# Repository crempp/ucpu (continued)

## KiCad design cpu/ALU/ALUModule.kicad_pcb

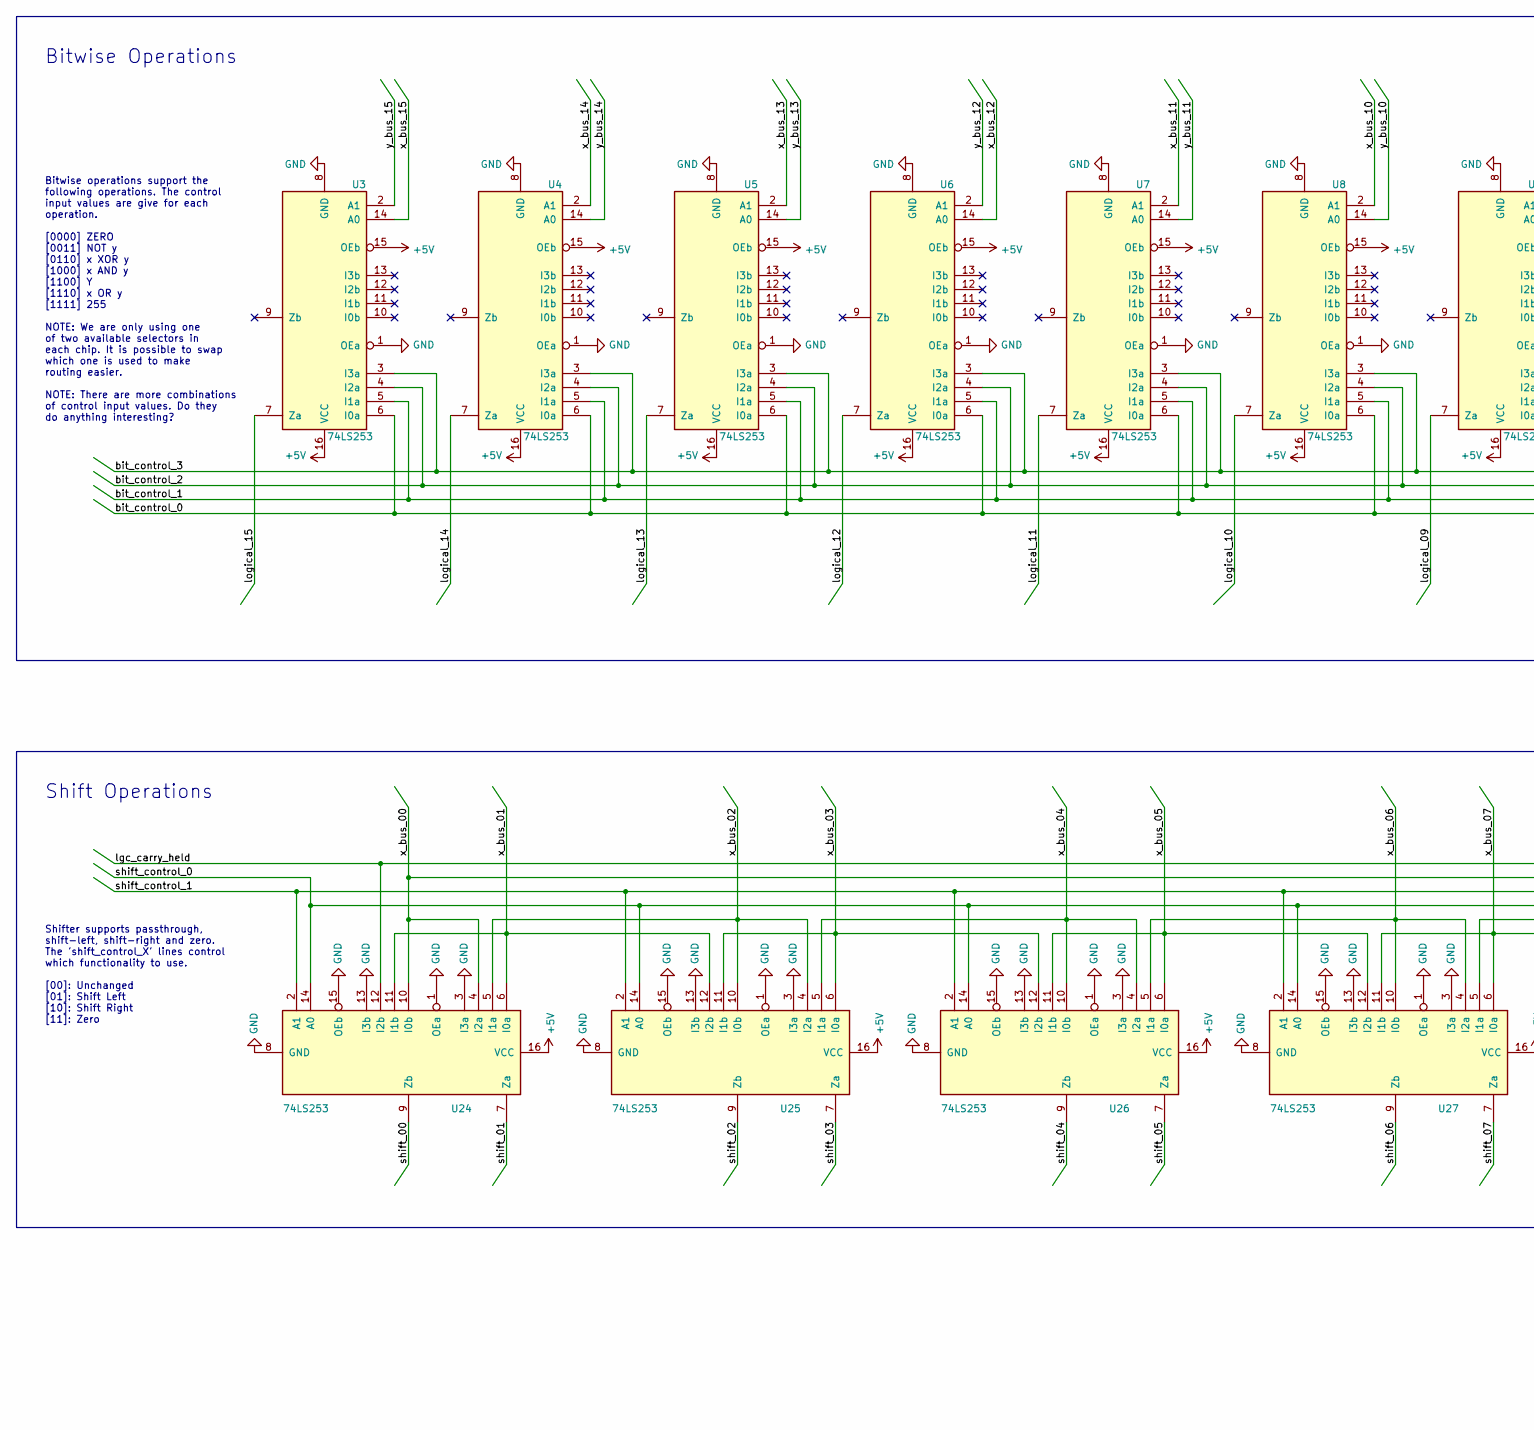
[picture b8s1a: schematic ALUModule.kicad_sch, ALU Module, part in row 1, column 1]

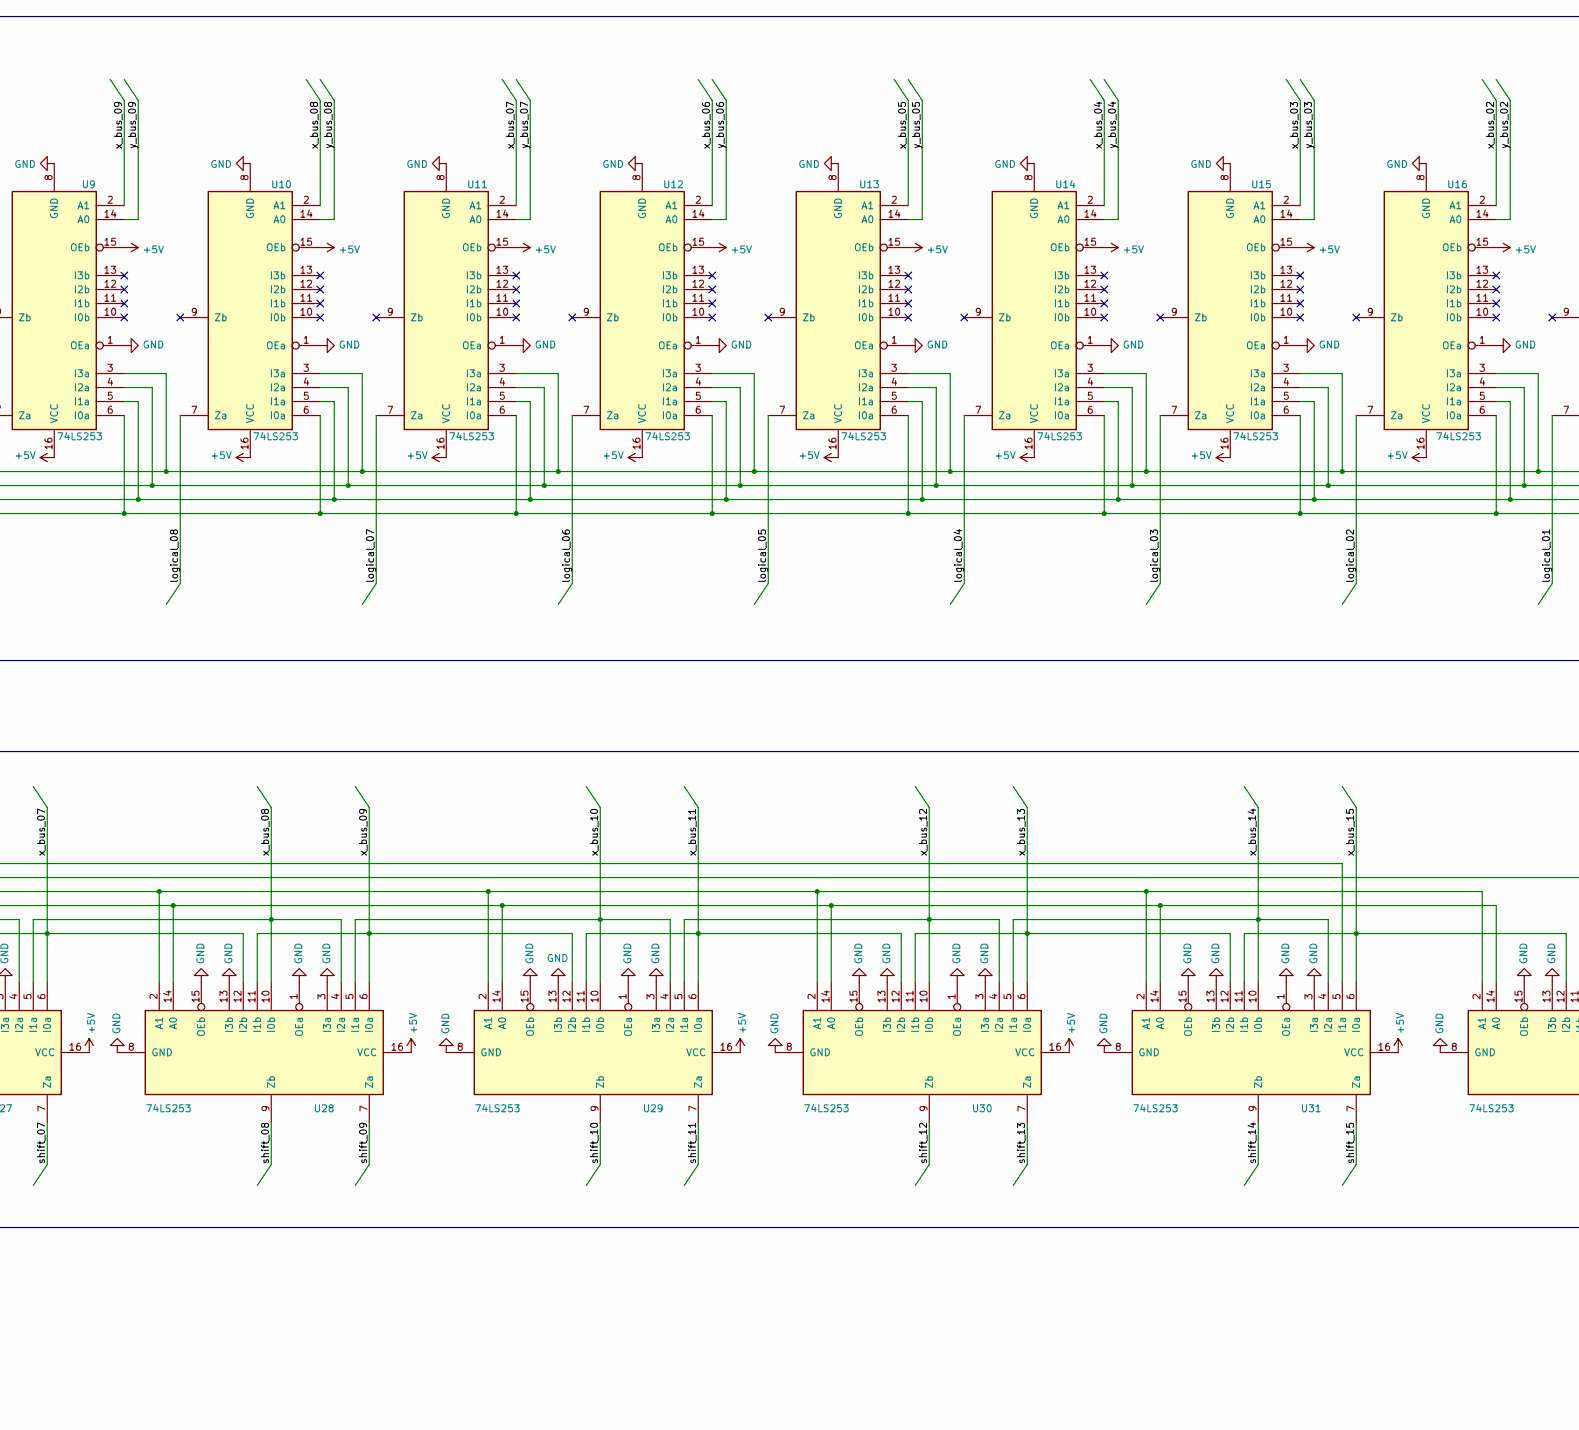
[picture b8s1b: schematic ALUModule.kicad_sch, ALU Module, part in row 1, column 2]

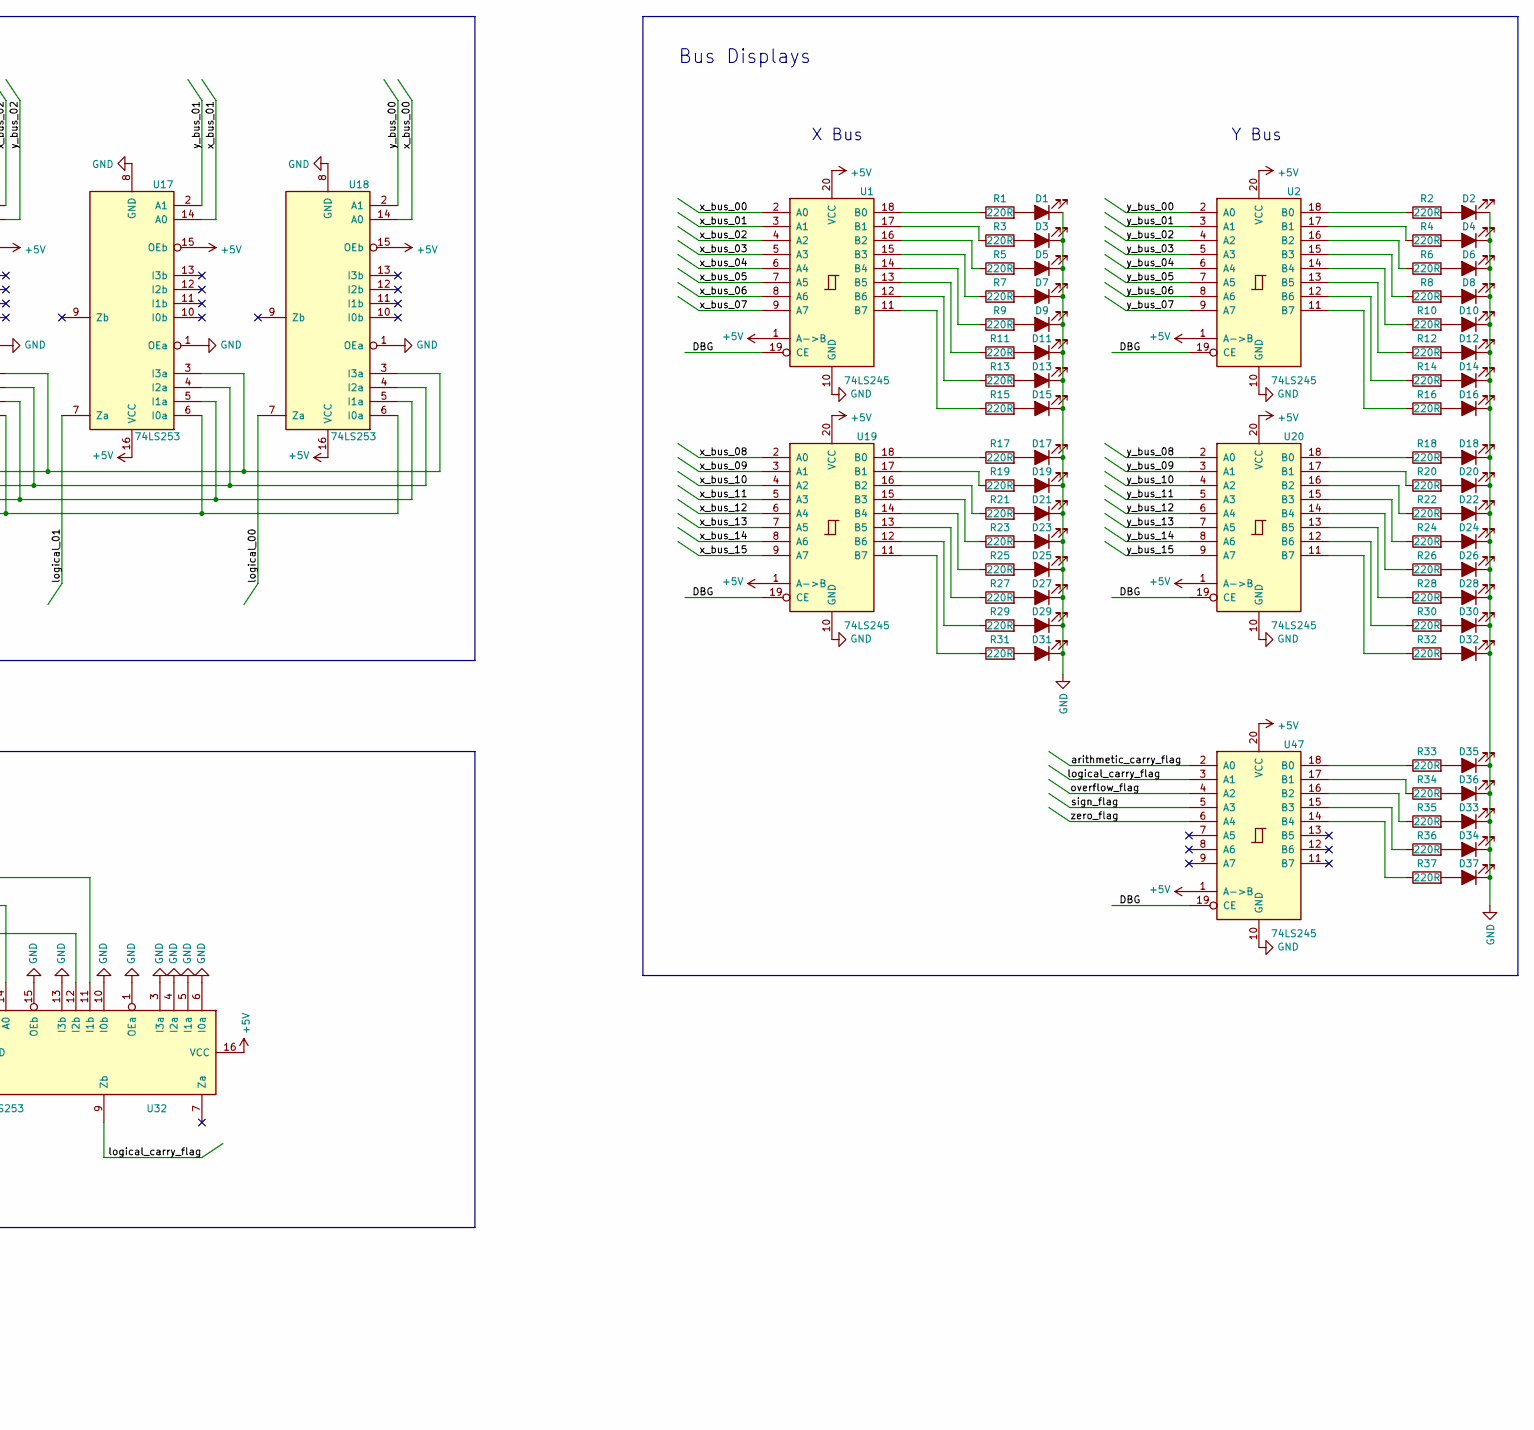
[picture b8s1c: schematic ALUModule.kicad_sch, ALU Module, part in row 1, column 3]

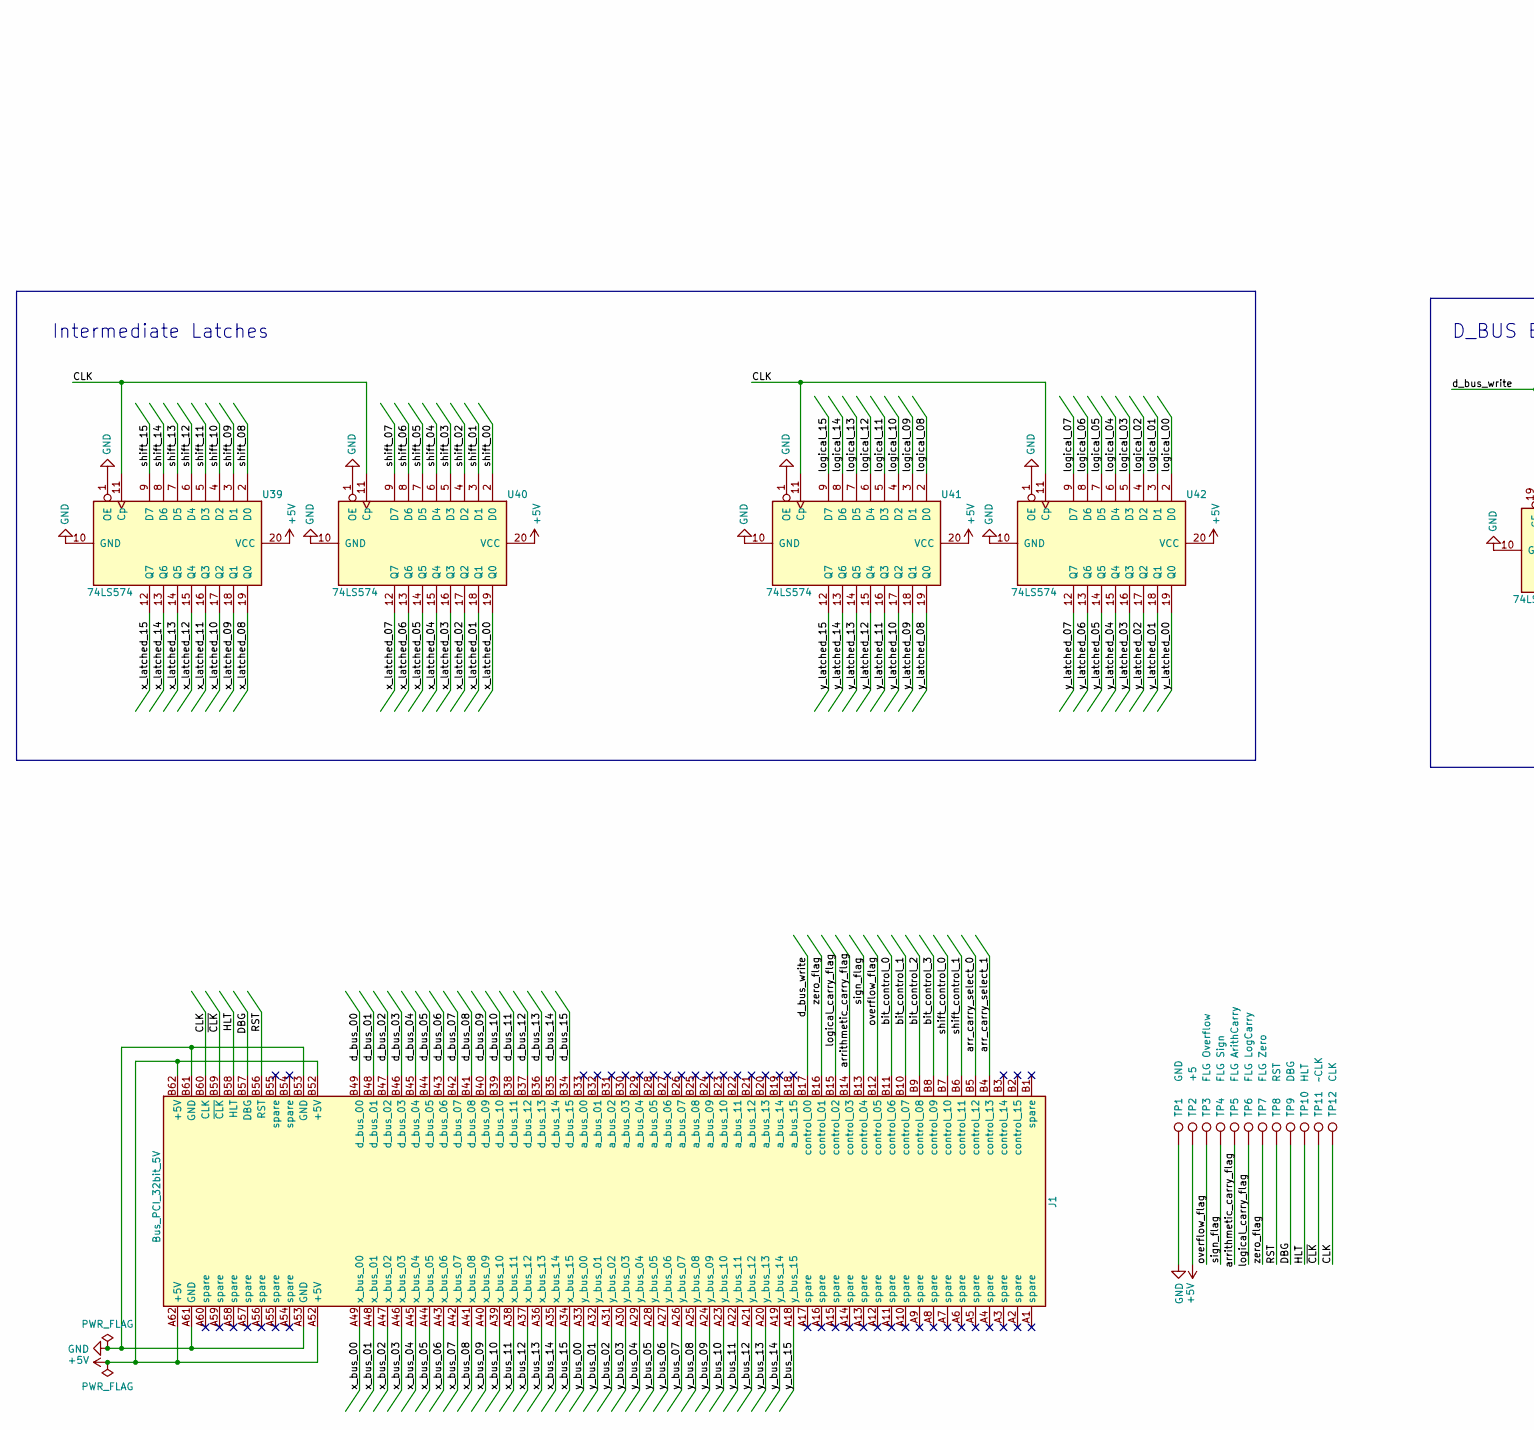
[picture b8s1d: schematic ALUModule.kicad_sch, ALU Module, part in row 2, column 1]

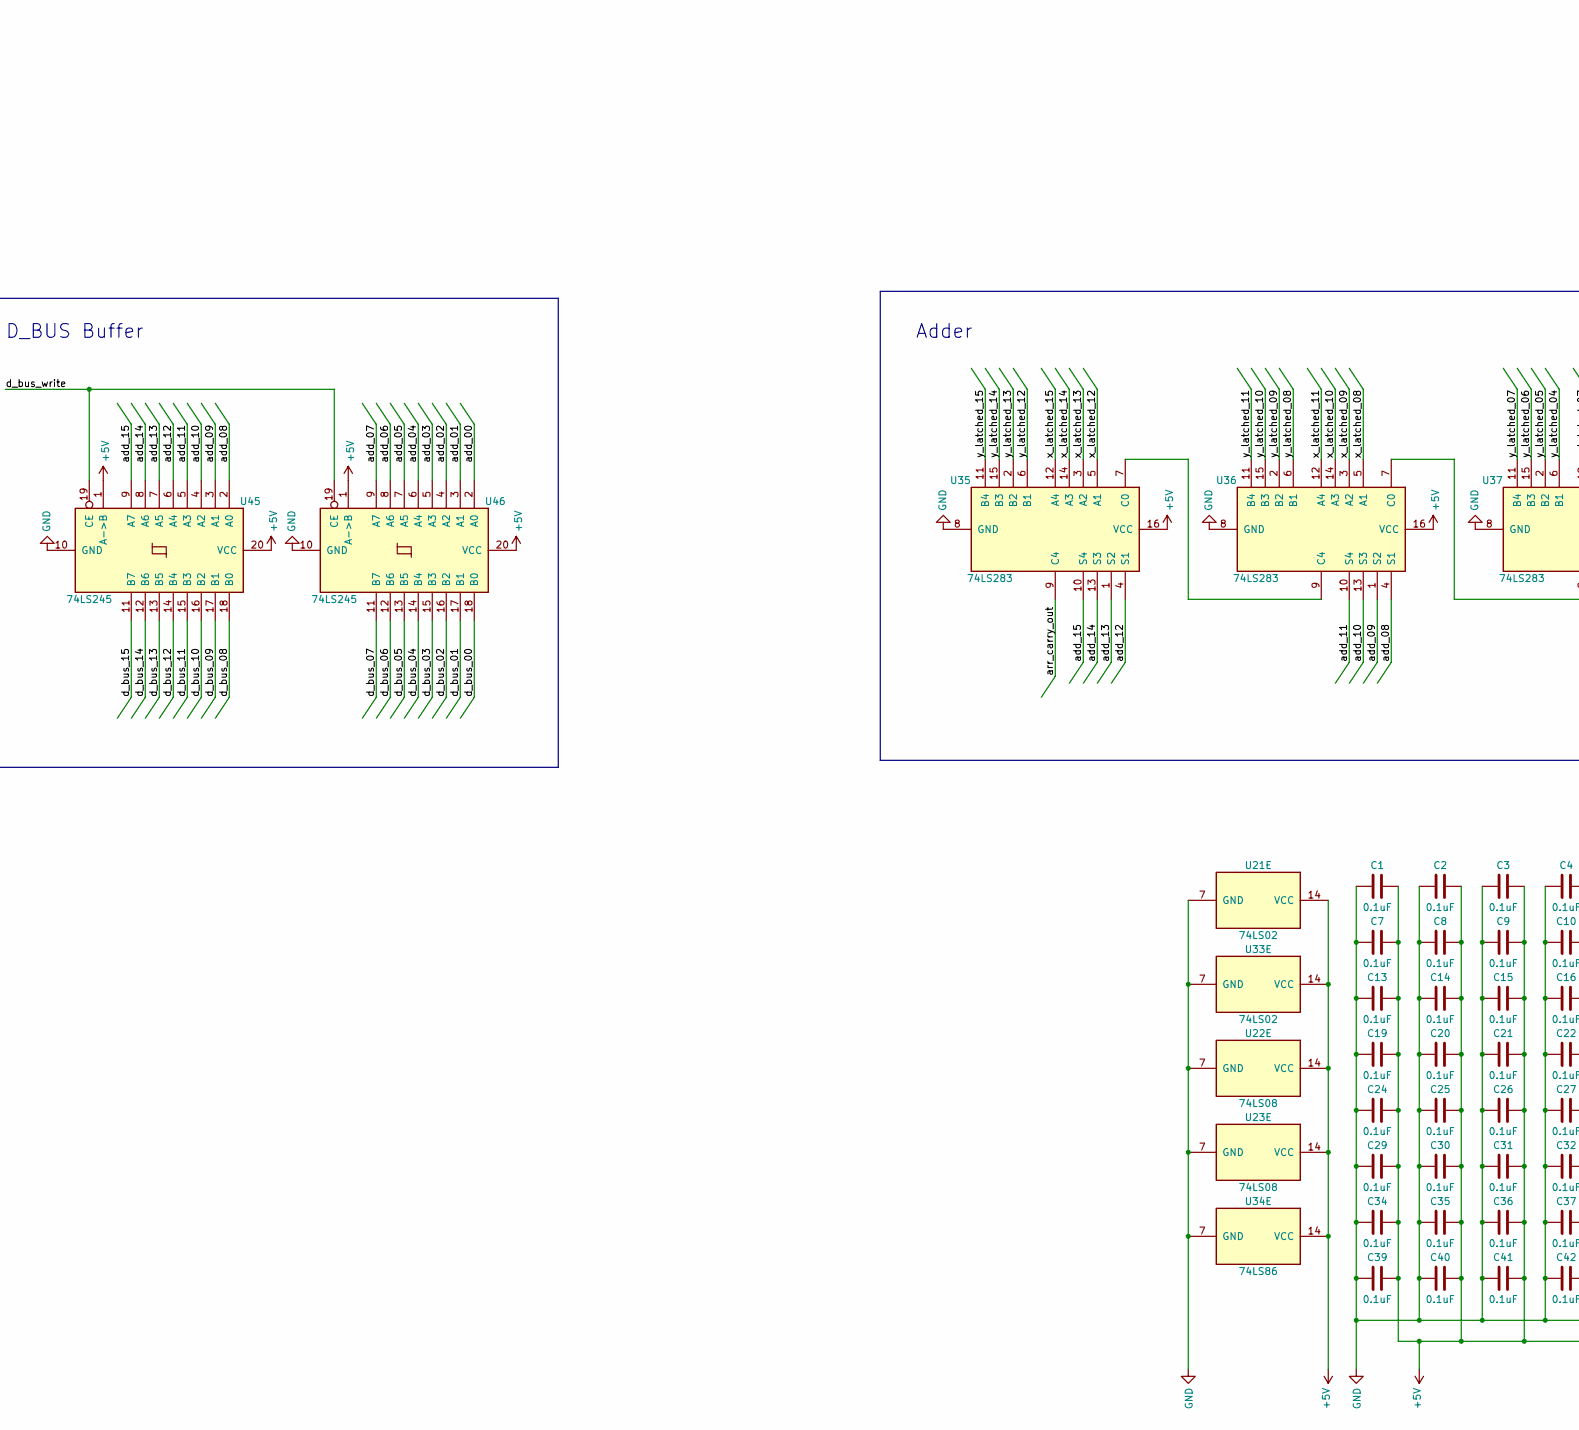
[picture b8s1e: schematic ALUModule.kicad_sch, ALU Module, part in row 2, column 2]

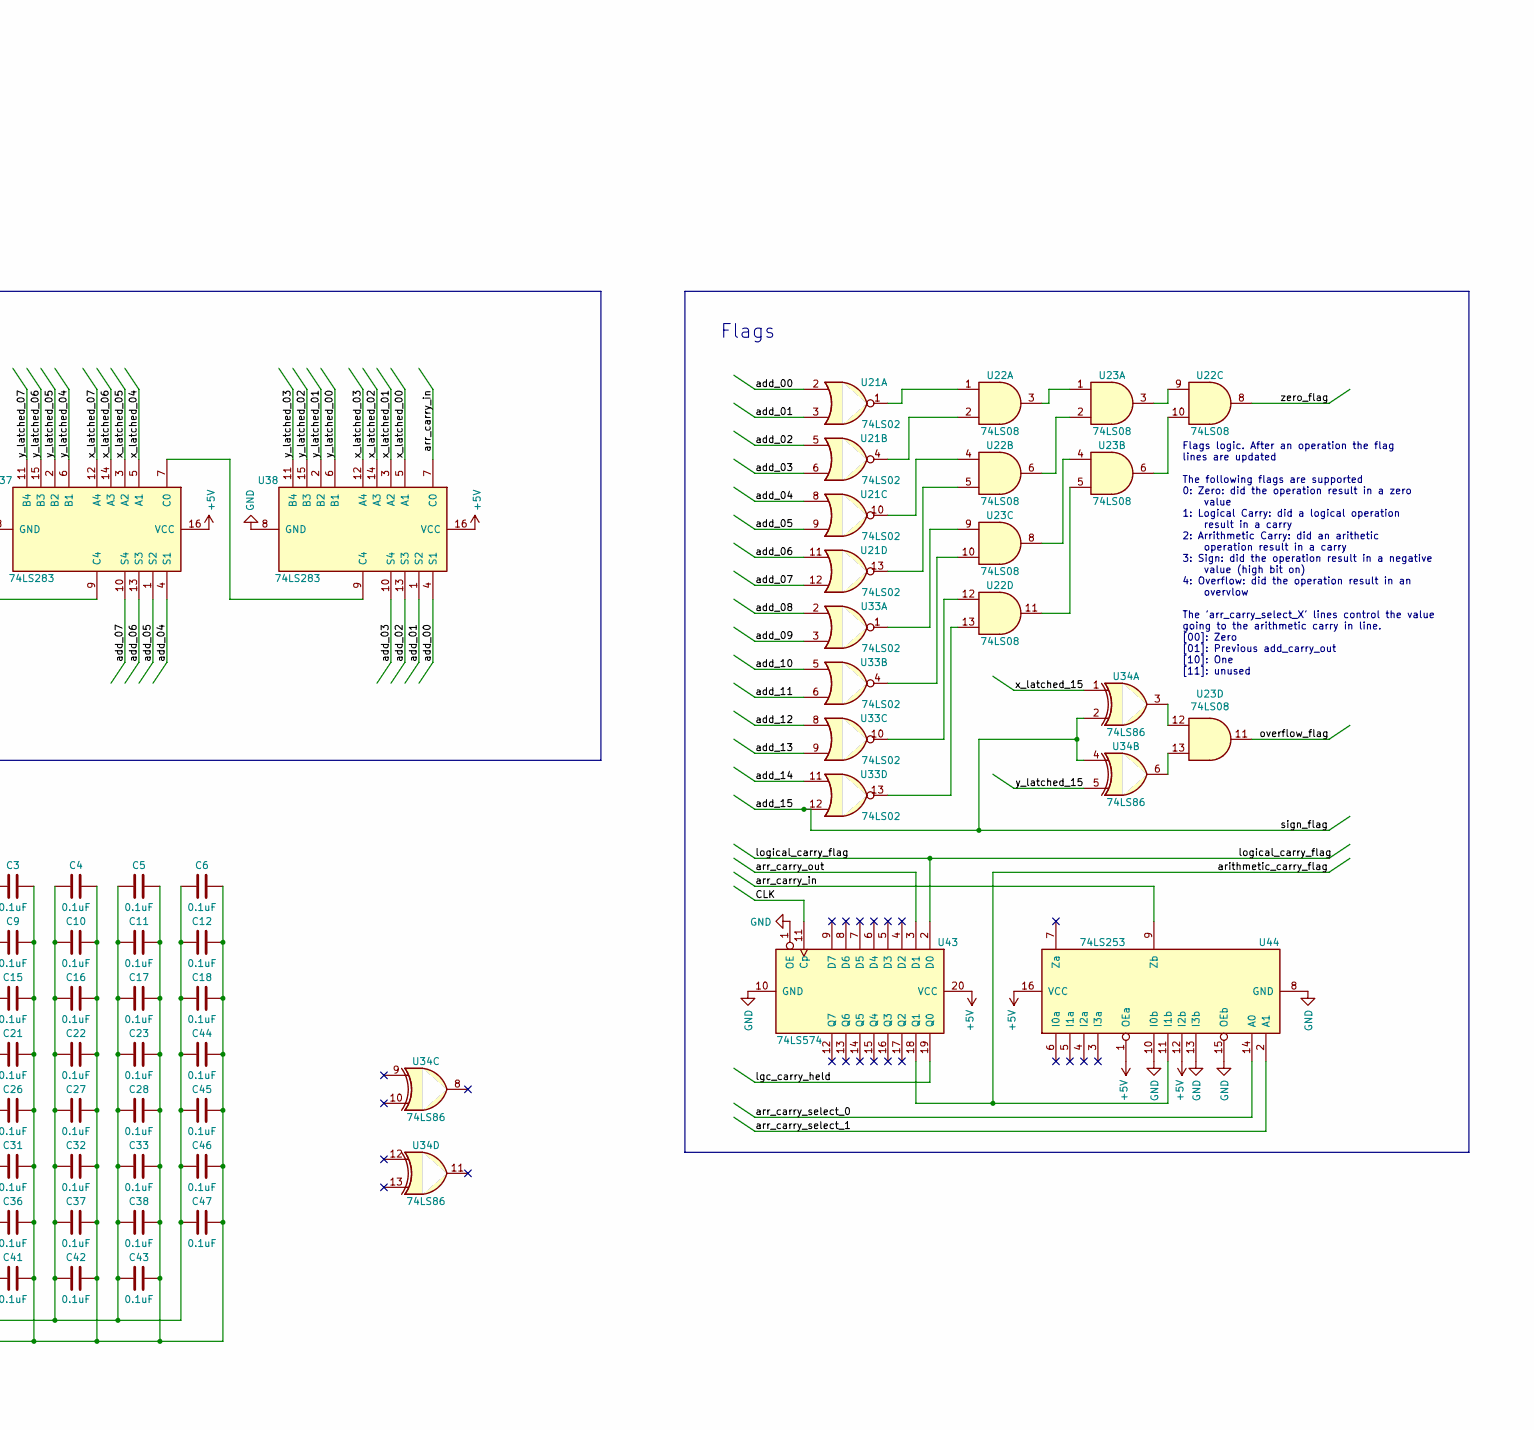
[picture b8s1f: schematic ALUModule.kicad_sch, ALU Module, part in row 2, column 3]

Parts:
C1, C2, C3, C4, C5, C6, C7, C8, C9, C10, C11, C12, C13, C14, C15, C16, C17, C18, C19, C20, C21, C22, C23, C24, C25, C26, C27, C28, C29, C30, C31, C32, C33, C34, C35, C36, C37, C38, C39, C40, C41, C42, C43, C44, C45, C46, C47: 0.1uF; C_0603_1608Metric_Pad1.05x0.95mm_HandSolder
D1, D2, D3, D4, D5, D6, D7, D8, D9, D10, D11, D12, D13, D14, D15, D16, D17, D18, D19, D20, D21, D22, D23, D24, D25, D26, D27, D28, D29, D30, D31, D32: LED_ALT; LED_1206_3216Metric_Pad1.42x1.75mm_HandSolder
D33: overflow; LED_1206_3216Metric_Pad1.42x1.75mm_HandSolder
D34: sign; LED_1206_3216Metric_Pad1.42x1.75mm_HandSolder
D35: arithmetic_carry; LED_1206_3216Metric_Pad1.42x1.75mm_HandSolder
D36: logical_carry; LED_1206_3216Metric_Pad1.42x1.75mm_HandSolder
D37: zero; LED_1206_3216Metric_Pad1.42x1.75mm_HandSolder
J1: Bus_PCI_32bit_5V; BUS_PCI
R1, R2, R3, R4, R5, R6, R7, R8, R9, R10, R11, R12, R13, R14, R15, R16, R17, R18, R19, R20, R21, R22, R23, R24, R25, R26, R27, R28, R29, R30, R31, R32, R33, R34, R35, R36, R37: 220R; R_0603_1608Metric_Pad1.05x0.95mm_HandSolder
TP1: GND; TestPoint_Pad_D1.5mm
TP2: +5; TestPoint_Pad_D1.5mm
TP3: FLG Overflow; TestPoint_Pad_D1.5mm
TP4: FLG Sign; TestPoint_Pad_D1.5mm
TP5: FLG ArithCarry; TestPoint_Pad_D1.5mm
TP6: FLG LogCarry; TestPoint_Pad_D1.5mm
TP7: FLG Zero; TestPoint_Pad_D1.5mm
TP8: RST; TestPoint_Pad_D1.5mm
TP9: DBG; TestPoint_Pad_D1.5mm
TP10: HLT; TestPoint_Pad_D1.5mm
TP11: ~CLK; TestPoint_Pad_D1.5mm
TP12: CLK; TestPoint_Pad_D1.5mm
U1, U2, U19, U20, U45, U46, U47: 74LS245; SOIC-20W_7.5x12.8mm_P1.27mm
U3, U4, U5, U6, U7, U8, U9, U10, U11, U12, U13, U14, U15, U16, U17, U18, U24, U25, U26, U27, U28, U29, U30, U31, U32, U44: 74LS253; SOIC-16_3.9x9.9mm_P1.27mm
U21, U33: 74LS02; SOIC-14_3.9x8.7mm_P1.27mm
U22, U23: 74LS08; SOIC-14_3.9x8.7mm_P1.27mm
U34: 74LS86; SOIC-14_3.9x8.7mm_P1.27mm
U35, U36, U37, U38: 74LS283; SOIC-16_3.9x9.9mm_P1.27mm
U39, U40, U41, U42, U43: 74LS574; SOIC-20W_7.5x12.8mm_P1.27mm

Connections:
+5V: C1.1, C2.1, C3.1, C4.1, C5.1, C6.1, C7.1, C8.1, C9.1, C10.1, C11.1, C12.1, C13.1, C14.1, C15.1, C16.1, C17.1, C18.1, C19.1, C20.1, C21.1, C22.1, C23.1, C24.1, C25.1, C26.1, C27.1, C28.1, C29.1, C30.1, C31.1, C32.1, C33.1, C34.1, C35.1, C36.1, C37.1, C38.1, C39.1, C40.1, C41.1, C42.1, C43.1, C44.1, C45.1, C46.1, C47.1, J1.A52 (+5V), J1.A62 (+5V), J1.B52 (+5V), J1.B62 (+5V), TP2.1, U1.1 (A->B), U1.20 (VCC), U2.1 (A->B), U2.20 (VCC), U3.15 (OEb), U3.16 (VCC), U4.15 (OEb), U4.16 (VCC), U5.15 (OEb), U5.16 (VCC), U6.15 (OEb), U6.16 (VCC), U7.15 (OEb), U7.16 (VCC), U8.15 (OEb), U8.16 (VCC), U9.15 (OEb), U9.16 (VCC), U10.15 (OEb), U10.16 (VCC), U11.15 (OEb), U11.16 (VCC), U12.15 (OEb), U12.16 (VCC), U13.15 (OEb), U13.16 (VCC), U14.15 (OEb), U14.16 (VCC), U15.15 (OEb), U15.16 (VCC), U16.15 (OEb), U16.16 (VCC), U17.15 (OEb), U17.16 (VCC), U18.15 (OEb), U18.16 (VCC), U19.1 (A->B), U19.20 (VCC), U20.1 (A->B), U20.20 (VCC), U21.14 (VCC), U22.14 (VCC)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
/CLK: J1.B60 (CLK), TP12.1, U39.11 (Cp), U40.11 (Cp), U41.11 (Cp), U42.11 (Cp), U43.11 (Cp)
/DBG: J1.B57 (DBG), TP9.1, U1.19 (CE), U2.19 (CE), U19.19 (CE), U20.19 (CE), U47.19 (CE)
/HLT: J1.B58 (HLT), TP10.1
/RST: J1.B56 (RST), TP8.1
/add_00: U21.2, U38.4 (S1), U46.2 (A0)
/add_01: U21.3, U38.1 (S2), U46.3 (A1)
/add_02: U21.5, U38.13 (S3), U46.4 (A2)
/add_03: U21.6, U38.10 (S4), U46.5 (A3)
/add_04: U21.8, U37.4 (S1), U46.6 (A4)
/add_05: U21.9, U37.1 (S2), U46.7 (A5)
/add_06: U21.11, U37.13 (S3), U46.8 (A6)
/add_07: U21.12, U37.10 (S4), U46.9 (A7)
/add_08: U33.2, U36.4 (S1), U45.2 (A0)
/add_09: U33.3, U36.1 (S2), U45.3 (A1)
/add_10: U33.5, U36.13 (S3), U45.4 (A2)
/add_11: U33.6, U36.10 (S4), U45.5 (A3)
/add_12: U33.8, U35.4 (S1), U45.6 (A4)
/add_13: U33.9, U35.1 (S2), U45.7 (A5)
/add_14: U33.11, U35.13 (S3), U45.8 (A6)
/add_15: J1.B13 (control_04), TP4.1, U33.12, U34.2, U34.4, U35.10 (S4), U45.9 (A7), U47.5 (A3)
/arithmetic_carry_flag: U43.18 (Q1), U44.11 (I1b), U47.2 (A0)
/arr_carry_in: U38.7 (C0), U44.9 (Zb)
/arr_carry_out: U35.9 (C4), U43.3 (D1)
/arr_carry_select_0: J1.B5 (control_12), U44.14 (A0)
/arr_carry_select_1: J1.B4 (control_13), U44.2 (A1)
/arrithmetic_carry_flag: J1.B14 (control_03), TP5.1
/bit_control_0: J1.B11 (control_06), U3.6 (I0a), U4.6 (I0a), U5.6 (I0a), U6.6 (I0a), U7.6 (I0a), U8.6 (I0a), U9.6 (I0a), U10.6 (I0a), U11.6 (I0a), U12.6 (I0a), U13.6 (I0a), U14.6 (I0a), U15.6 (I0a), U16.6 (I0a), U17.6 (I0a), U18.6 (I0a)
/bit_control_1: J1.B10 (control_07), U3.5 (I1a), U4.5 (I1a), U5.5 (I1a), U6.5 (I1a), U7.5 (I1a), U8.5 (I1a), U9.5 (I1a), U10.5 (I1a), U11.5 (I1a), U12.5 (I1a), U13.5 (I1a), U14.5 (I1a), U15.5 (I1a), U16.5 (I1a), U17.5 (I1a), U18.5 (I1a)
/bit_control_2: J1.B9 (control_08), U3.4 (I2a), U4.4 (I2a), U5.4 (I2a), U6.4 (I2a), U7.4 (I2a), U8.4 (I2a), U9.4 (I2a), U10.4 (I2a), U11.4 (I2a), U12.4 (I2a), U13.4 (I2a), U14.4 (I2a), U15.4 (I2a), U16.4 (I2a), U17.4 (I2a), U18.4 (I2a)
/bit_control_3: J1.B8 (control_09), U3.3 (I3a), U4.3 (I3a), U5.3 (I3a), U6.3 (I3a), U7.3 (I3a), U8.3 (I3a), U9.3 (I3a), U10.3 (I3a), U11.3 (I3a), U12.3 (I3a), U13.3 (I3a), U14.3 (I3a), U15.3 (I3a), U16.3 (I3a), U17.3 (I3a), U18.3 (I3a)
/d_bus_00: J1.B49 (d_bus_00), U46.18 (B0)
/d_bus_01: J1.B48 (d_bus_01), U46.17 (B1)
/d_bus_02: J1.B47 (d_bus_02), U46.16 (B2)
/d_bus_03: J1.B46 (d_bus_03), U46.15 (B3)
/d_bus_04: J1.B45 (d_bus_04), U46.14 (B4)
/d_bus_05: J1.B44 (d_bus_05), U46.13 (B5)
/d_bus_06: J1.B43 (d_bus_06), U46.12 (B6)
/d_bus_07: J1.B42 (d_bus_07), U46.11 (B7)
/d_bus_08: J1.B41 (d_bus_08), U45.18 (B0)
/d_bus_09: J1.B40 (d_bus_09), U45.17 (B1)
/d_bus_10: J1.B39 (d_bus_10), U45.16 (B2)
/d_bus_11: J1.B38 (d_bus_11), U45.15 (B3)
/d_bus_12: J1.B37 (d_bus_12), U45.14 (B4)
/d_bus_13: J1.B36 (d_bus_13), U45.13 (B5)
/d_bus_14: J1.B35 (d_bus_14), U45.12 (B6)
/d_bus_15: J1.B34 (d_bus_15), U45.11 (B7)
/d_bus_write: J1.B17 (control_00), U45.19 (CE), U46.19 (CE)
/lgc_carry_held: U24.12 (I2b), U31.5 (I1a), U43.19 (Q0)
/logical_00: U18.7 (Za), U42.2 (D0)
/logical_01: U17.7 (Za), U42.3 (D1)
/logical_02: U16.7 (Za), U42.4 (D2)
/logical_03: U15.7 (Za), U42.5 (D3)
/logical_04: U14.7 (Za), U42.6 (D4)
/logical_05: U13.7 (Za), U42.7 (D5)
/logical_06: U12.7 (Za), U42.8 (D6)
/logical_07: U11.7 (Za), U42.9 (D7)
/logical_08: U10.7 (Za), U41.2 (D0)
/logical_09: U9.7 (Za), U41.3 (D1)
/logical_10: U8.7 (Za), U41.4 (D2)
/logical_11: U7.7 (Za), U41.5 (D3)
/logical_12: U6.7 (Za), U41.6 (D4)
/logical_13: U5.7 (Za), U41.7 (D5)
/logical_14: U4.7 (Za), U41.8 (D6)
/logical_15: U3.7 (Za), U41.9 (D7)
/logical_carry_flag: J1.B15 (control_02), TP6.1, U32.9 (Zb), U43.2 (D0), U47.3 (A1)
/overflow_flag: J1.B12 (control_05), TP3.1, U23.11, U47.4 (A2)
/shift_00: U24.9 (Zb), U40.2 (D0)
/shift_01: U24.7 (Za), U40.3 (D1)
/shift_02: U25.9 (Zb), U40.4 (D2)
/shift_03: U25.7 (Za), U40.5 (D3)
/shift_04: U26.9 (Zb), U40.6 (D4)
/shift_05: U26.7 (Za), U40.7 (D5)
/shift_06: U27.9 (Zb), U40.8 (D6)
/shift_07: U27.7 (Za), U40.9 (D7)
/shift_08: U28.9 (Zb), U39.2 (D0)
/shift_09: U28.7 (Za), U39.3 (D1)
/shift_10: U29.9 (Zb), U39.4 (D2)
/shift_11: U29.7 (Za), U39.5 (D3)
/shift_12: U30.9 (Zb), U39.6 (D4)
/shift_13: U30.7 (Za), U39.7 (D5)
/shift_14: U31.9 (Zb), U39.8 (D6)
/shift_15: U31.7 (Za), U39.9 (D7)
/shift_control_0: J1.B7 (control_10), U24.14 (A0), U25.14 (A0), U26.14 (A0), U27.14 (A0), U28.14 (A0), U29.14 (A0), U30.14 (A0), U31.14 (A0), U32.14 (A0)
/shift_control_1: J1.B6 (control_11), U24.2 (A1), U25.2 (A1), U26.2 (A1), U27.2 (A1), U28.2 (A1), U29.2 (A1), U30.2 (A1), U31.2 (A1), U32.2 (A1)
/x_bus_00: J1.A49 (x_bus_00), U1.2 (A0), U18.14 (A0), U24.4 (I2a), U24.10 (I0b), U32.11 (I1b)
/x_bus_01: J1.A48 (x_bus_01), U1.3 (A1), U17.14 (A0), U24.6 (I0a), U24.11 (I1b), U25.12 (I2b)
/x_bus_02: J1.A47 (x_bus_02), U1.4 (A2), U16.2 (A1), U24.5 (I1a), U25.4 (I2a), U25.10 (I0b)
/x_bus_03: J1.A46 (x_bus_03), U1.5 (A3), U15.2 (A1), U25.6 (I0a), U25.11 (I1b), U26.12 (I2b)
/x_bus_04: J1.A45 (x_bus_04), U1.6 (A4), U14.2 (A1), U25.5 (I1a), U26.4 (I2a), U26.10 (I0b)
/x_bus_05: J1.A44 (x_bus_05), U1.7 (A5), U13.2 (A1), U26.6 (I0a), U26.11 (I1b), U27.12 (I2b)
/x_bus_06: J1.A43 (x_bus_06), U1.8 (A6), U12.2 (A1), U26.5 (I1a), U27.4 (I2a), U27.10 (I0b)
/x_bus_07: J1.A42 (x_bus_07), U1.9 (A7), U11.2 (A1), U27.6 (I0a), U27.11 (I1b), U28.12 (I2b)
/x_bus_08: J1.A41 (x_bus_08), U10.2 (A1), U19.2 (A0), U27.5 (I1a), U28.4 (I2a), U28.10 (I0b)
/x_bus_09: J1.A40 (x_bus_09), U9.2 (A1), U19.3 (A1), U28.6 (I0a), U28.11 (I1b), U29.12 (I2b)
/x_bus_10: J1.A39 (x_bus_10), U8.2 (A1), U19.4 (A2), U28.5 (I1a), U29.4 (I2a), U29.10 (I0b)
/x_bus_11: J1.A38 (x_bus_11), U7.2 (A1), U19.5 (A3), U29.6 (I0a), U29.11 (I1b), U30.12 (I2b)
/x_bus_12: J1.A37 (x_bus_12), U6.14 (A0), U19.6 (A4), U29.5 (I1a), U30.4 (I2a), U30.10 (I0b)
/x_bus_13: J1.A36 (x_bus_13), U5.2 (A1), U19.7 (A5), U30.6 (I0a), U30.11 (I1b), U31.12 (I2b)
/x_bus_14: J1.A35 (x_bus_14), U4.2 (A1), U19.8 (A6), U30.5 (I1a), U31.4 (I2a), U31.10 (I0b)
/x_bus_15: J1.A34 (x_bus_15), U3.14 (A0), U19.9 (A7), U31.6 (I0a), U31.11 (I1b), U32.12 (I2b)
/x_latched_00: U38.5 (A1), U40.19 (Q0)
/x_latched_01: U38.3 (A2), U40.18 (Q1)
/x_latched_02: U38.14 (A3), U40.17 (Q2)
/x_latched_03: U38.12 (A4), U40.16 (Q3)
/x_latched_04: U37.5 (A1), U40.15 (Q4)
/x_latched_05: U37.3 (A2), U40.14 (Q5)
/x_latched_06: U37.14 (A3), U40.13 (Q6)
/x_latched_07: U37.12 (A4), U40.12 (Q7)
/x_latched_08: U36.5 (A1), U39.19 (Q0)
/x_latched_09: U36.3 (A2), U39.18 (Q1)
/x_latched_10: U36.14 (A3), U39.17 (Q2)
/x_latched_11: U36.12 (A4), U39.16 (Q3)
/x_latched_12: U35.5 (A1), U39.15 (Q4)
/x_latched_13: U35.3 (A2), U39.14 (Q5)
/x_latched_14: U35.14 (A3), U39.13 (Q6)
/x_latched_15: U34.1, U35.12 (A4), U39.12 (Q7)
/y_bus_00: J1.A33 (y_bus_00), U2.2 (A0), U18.2 (A1)
/y_bus_01: J1.A32 (y_bus_01), U2.3 (A1), U17.2 (A1)
/y_bus_02: J1.A31 (y_bus_02), U2.4 (A2), U16.14 (A0)
/y_bus_03: J1.A30 (y_bus_03), U2.5 (A3), U15.14 (A0)
/y_bus_04: J1.A29 (y_bus_04), U2.6 (A4), U14.14 (A0)
/y_bus_05: J1.A28 (y_bus_05), U2.7 (A5), U13.14 (A0)
/y_bus_06: J1.A27 (y_bus_06), U2.8 (A6), U12.14 (A0)
/y_bus_07: J1.A26 (y_bus_07), U2.9 (A7), U11.14 (A0)
/y_bus_08: J1.A25 (y_bus_08), U10.14 (A0), U20.2 (A0)
/y_bus_09: J1.A24 (y_bus_09), U9.14 (A0), U20.3 (A1)
/y_bus_10: J1.A23 (y_bus_10), U8.14 (A0), U20.4 (A2)
/y_bus_11: J1.A22 (y_bus_11), U7.14 (A0), U20.5 (A3)
/y_bus_12: J1.A21 (y_bus_12), U6.2 (A1), U20.6 (A4)
/y_bus_13: J1.A20 (y_bus_13), U5.14 (A0), U20.7 (A5)
/y_bus_14: J1.A19 (y_bus_14), U4.14 (A0), U20.8 (A6)
/y_bus_15: J1.A18 (y_bus_15), U3.2 (A1), U20.9 (A7)
/y_latched_00: U38.6 (B1), U42.19 (Q0)
/y_latched_01: U38.2 (B2), U42.18 (Q1)
/y_latched_02: U38.15 (B3), U42.17 (Q2)
/y_latched_03: U38.11 (B4), U42.16 (Q3)
/y_latched_04: U37.6 (B1), U42.15 (Q4)
/y_latched_05: U37.2 (B2), U42.14 (Q5)
/y_latched_06: U37.15 (B3), U42.13 (Q6)
/y_latched_07: U37.11 (B4), U42.12 (Q7)
/y_latched_08: U36.6 (B1), U41.19 (Q0)
/y_latched_09: U36.2 (B2), U41.18 (Q1)
/y_latched_10: U36.15 (B3), U41.17 (Q2)
/y_latched_11: U36.11 (B4), U41.16 (Q3)
/y_latched_12: U35.6 (B1), U41.15 (Q4)
/y_latched_13: U35.2 (B2), U41.14 (Q5)
/y_latched_14: U35.15 (B3), U41.13 (Q6)
/y_latched_15: U34.5, U35.11 (B4), U41.12 (Q7)
/zero_flag: J1.B16 (control_01), TP7.1, U22.8, U47.6 (A4)
/~CLK: J1.B59 (~CLK), TP11.1
GND: C1.2, C2.2, C3.2, C4.2, C5.2, C6.2, C7.2, C8.2, C9.2, C10.2, C11.2, C12.2, C13.2, C14.2, C15.2, C16.2, C17.2, C18.2, C19.2, C20.2, C21.2, C22.2, C23.2, C24.2, C25.2, C26.2, C27.2, C28.2, C29.2, C30.2, C31.2, C32.2, C33.2, C34.2, C35.2, C36.2, C37.2, C38.2, C39.2, C40.2, C41.2, C42.2, C43.2, C44.2, C45.2, C46.2, C47.2, D1.1 (K), D2.1 (K), D3.1 (K), D4.1 (K), D5.1 (K), D6.1 (K), D7.1 (K), D8.1 (K), D9.1 (K), D10.1 (K), D11.1 (K), D12.1 (K), D13.1 (K), D14.1 (K), D15.1 (K), D16.1 (K), D17.1 (K), D18.1 (K), D19.1 (K), D20.1 (K), D21.1 (K), D22.1 (K), D23.1 (K), D24.1 (K), D25.1 (K), D26.1 (K), D27.1 (K), D28.1 (K), D29.1 (K), D30.1 (K), D31.1 (K), D32.1 (K), D33.1 (K), D34.1 (K), D35.1 (K), D36.1 (K), D37.1 (K), J1.A53 (GND), J1.A61 (GND), J1.B53 (GND), J1.B61 (GND), TP1.1, U1.10 (GND), U2.10 (GND), U3.1 (OEa), U3.8 (GND), U4.1 (OEa)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
unnamed: D1.2 (A), R1.2
unnamed: D2.2 (A), R2.2
unnamed: D3.2 (A), R3.2
unnamed: D4.2 (A), R4.2
unnamed: D5.2 (A), R5.2
unnamed: D6.2 (A), R6.2
unnamed: D7.2 (A), R7.2
unnamed: D8.2 (A), R8.2
unnamed: D9.2 (A), R9.2
unnamed: D10.2 (A), R10.2
unnamed: D11.2 (A), R11.2
unnamed: D12.2 (A), R12.2
unnamed: D13.2 (A), R13.2
unnamed: D14.2 (A), R14.2
unnamed: D15.2 (A), R15.2
unnamed: D16.2 (A), R16.2
unnamed: D17.2 (A), R17.2
unnamed: D18.2 (A), R18.2
unnamed: D19.2 (A), R19.2
unnamed: D20.2 (A), R20.2
unnamed: D21.2 (A), R21.2
unnamed: D22.2 (A), R22.2
unnamed: D23.2 (A), R23.2
unnamed: D24.2 (A), R24.2
unnamed: D25.2 (A), R25.2
unnamed: D26.2 (A), R26.2
unnamed: D27.2 (A), R27.2
unnamed: D28.2 (A), R28.2
unnamed: D29.2 (A), R29.2
unnamed: D30.2 (A), R30.2
unnamed: D31.2 (A), R31.2
unnamed: D32.2 (A), R32.2
unnamed: D33.2 (A), R35.2
unnamed: D34.2 (A), R36.2
unnamed: D35.2 (A), R33.2
unnamed: D36.2 (A), R34.2
unnamed: D37.2 (A), R37.2
unnamed: R1.1, U1.18 (B0)
unnamed: R2.1, U2.18 (B0)
unnamed: R3.1, U1.17 (B1)
unnamed: R4.1, U2.17 (B1)
unnamed: R5.1, U1.16 (B2)
unnamed: R6.1, U2.16 (B2)
unnamed: R7.1, U1.15 (B3)
unnamed: R8.1, U2.15 (B3)
unnamed: R9.1, U1.14 (B4)
unnamed: R10.1, U2.14 (B4)
unnamed: R11.1, U1.13 (B5)
unnamed: R12.1, U2.13 (B5)
unnamed: R13.1, U1.12 (B6)
unnamed: R14.1, U2.12 (B6)
unnamed: R15.1, U1.11 (B7)
unnamed: R16.1, U2.11 (B7)
unnamed: R17.1, U19.18 (B0)
unnamed: R18.1, U20.18 (B0)
unnamed: R19.1, U19.17 (B1)
unnamed: R20.1, U20.17 (B1)
unnamed: R21.1, U19.16 (B2)
unnamed: R22.1, U20.16 (B2)
unnamed: R23.1, U19.15 (B3)
unnamed: R24.1, U20.15 (B3)
unnamed: R25.1, U19.14 (B4)
unnamed: R26.1, U20.14 (B4)
unnamed: R27.1, U19.13 (B5)
unnamed: R28.1, U20.13 (B5)
unnamed: R29.1, U19.12 (B6)
unnamed: R30.1, U20.12 (B6)
unnamed: R31.1, U19.11 (B7)
unnamed: R32.1, U20.11 (B7)
unnamed: R33.1, U47.18 (B0)
unnamed: R34.1, U47.17 (B1)
unnamed: R35.1, U47.16 (B2)
unnamed: R36.1, U47.15 (B3)
unnamed: R37.1, U47.14 (B4)
unnamed: U21.1, U22.1
unnamed: U21.4, U22.2
unnamed: U21.10, U22.4
unnamed: U21.13, U22.5
unnamed: U22.3, U23.1
unnamed: U22.6, U23.2
unnamed: U22.9, U23.3
unnamed: U22.10, U23.6
unnamed: U22.11, U23.5
unnamed: U22.12, U33.10
unnamed: U22.13, U33.13
unnamed: U23.4, U23.8
unnamed: U23.9, U33.1
unnamed: U23.10, U33.4
unnamed: U23.12, U34.3
unnamed: U23.13, U34.6
unnamed: U35.7 (C0), U36.9 (C4)
unnamed: U36.7 (C0), U37.9 (C4)
unnamed: U37.7 (C0), U38.9 (C4)

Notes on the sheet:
Flags
Bus Displays
Shifter supports passthrough, shift-left, shift-right and zero. The 'shift_control_X' lines control which functionality to use. [00]: Unchanged [01]: Shift Left [10]: Shift Right [11]: Zero
D_BUS Buffer
Intermediate Latches
X Bus
Flags logic. After an operation the flag lines are updated The following flags are supported 0: Zero: did the operation result in a zero value 1: Logical Carry: did a logical operation result in a carry 2: Arrithmetic Carry: did an arithetic operation result in a carry 3: Sign: did the operation re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
Adder
Bitwise Operations
Shift Operations
Y Bus
Bitwise operations support the following operations. The control input values are give for each operation. [0000] ZERO [0011] NOT y [0110] x XOR y [1000] x AND y [1100] Y [1110] x OR y [1111] 255 NOTE: We are only using one of two available selectors in each chip. It is possible to swap which one i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

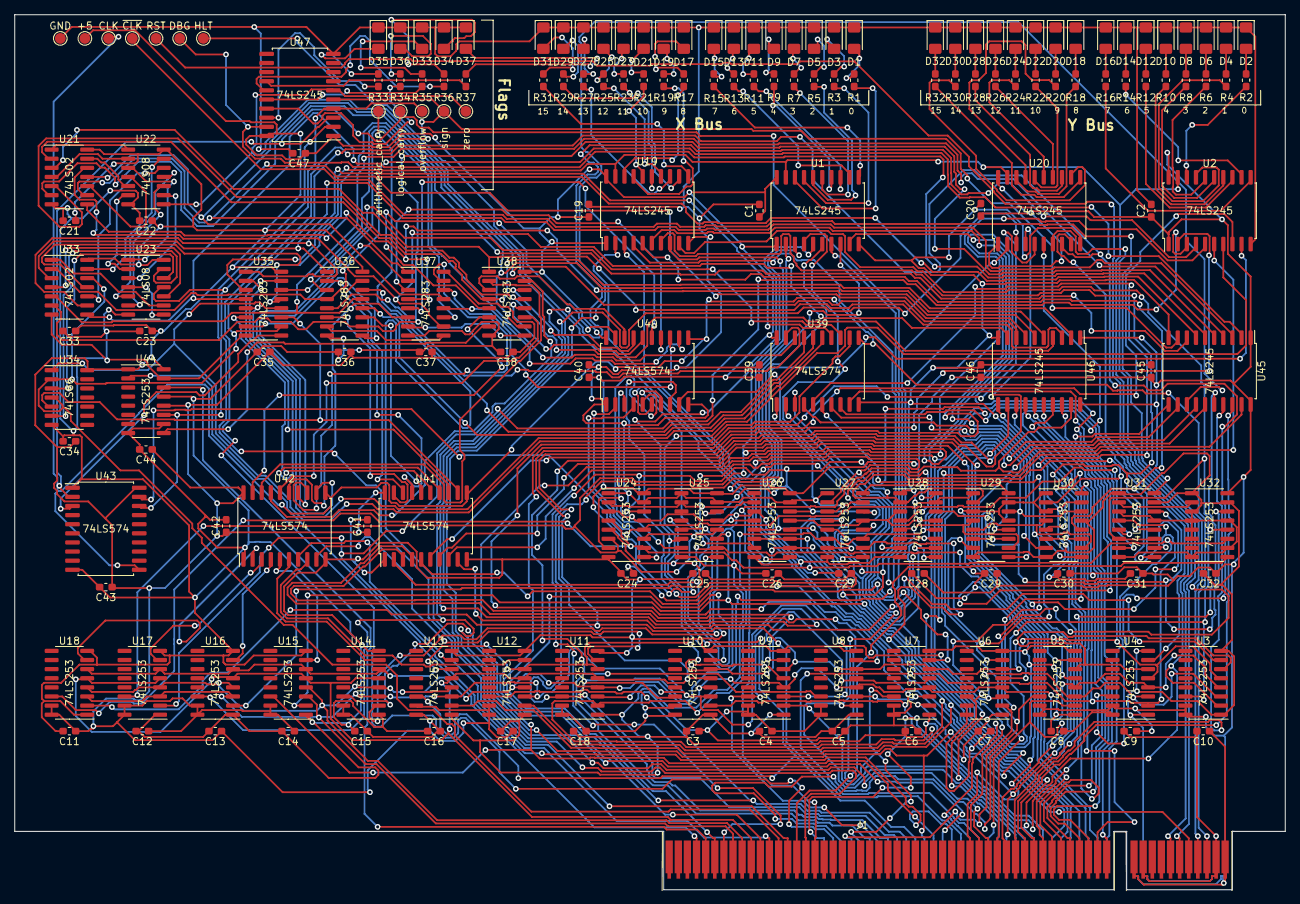
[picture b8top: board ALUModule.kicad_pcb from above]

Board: 2 copper layers, 177.0 x 121.9 mm, 181 parts (0 on the bottom side), 245 nets.

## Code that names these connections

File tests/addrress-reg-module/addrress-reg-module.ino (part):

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
// Control pin definitions
#define CLOCK 2
#define D_BUS_READ 3
#define D_BUS_WRITE 4
#define A_BUS_WRITE 5
#define REG_INC 6
#define REG_DEC 7
#define REG_CARRY 8
#define REG_BORROW 9
#define RESET 10

unsigned int loop_count = 1;
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  
  // Setup pins
  pinMode(CLOCK, OUTPUT);
  pinMode(D_BUS_READ, OUTPUT);
  pinMode(D_BUS_WRITE, OUTPUT);
  pinMode(A_BUS_WRITE, OUTPUT);
  pinMode(REG_INC, OUTPUT);
  pinMode(REG_DEC, OUTPUT);
  pinMode(REG_CARRY, INPUT);
  pinMode(REG_BORROW, INPUT);
  pinMode(RESET, OUTPUT);
  bus_pin_mode(abus, OUTPUT);
  bus_pin_mode(dbus, INPUT);
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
